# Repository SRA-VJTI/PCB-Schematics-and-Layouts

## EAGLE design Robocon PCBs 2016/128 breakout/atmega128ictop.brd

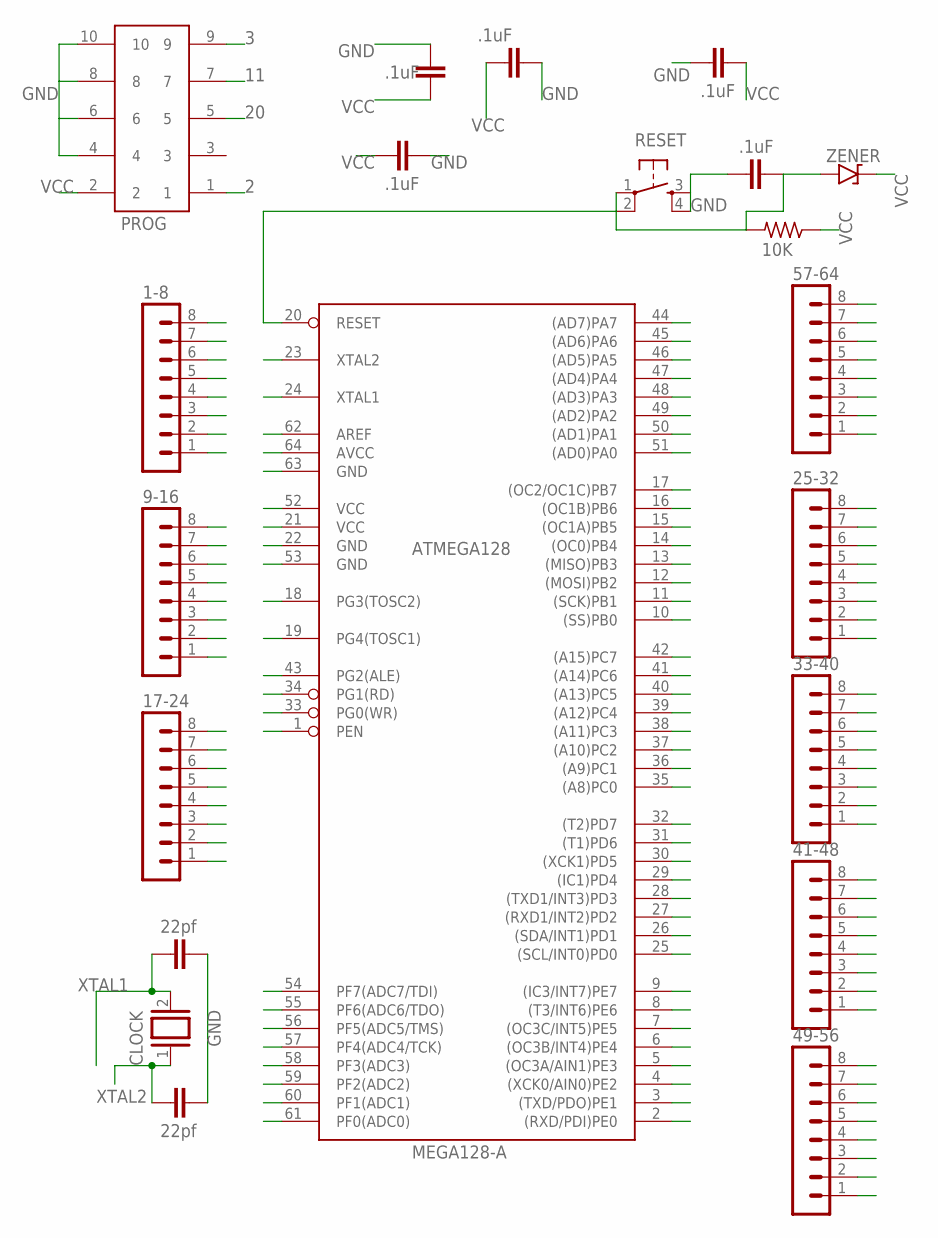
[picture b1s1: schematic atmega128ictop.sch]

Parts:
1-8, 9-16, 17-24, 25-32, 33-40, 41-48, 49-56, 57-64: MA08-1
ATMEGA128: MEGA128-A; TQFP64
C1, C2, C5, C6, C7: .1uF; C5B2.5
C3, C4: 22pf; C5B2.5
CLOCK: XTAL/S; QS
D1: ZENER; DO35-2
PROG: 61201021621
R1: 10K; 0204/5
RESET: DTS-6

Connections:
1: 1-8.1, ATMEGA128.1 (PEN)
2: 1-8.2, ATMEGA128.2 ((RXD/PDI)PE0), PROG.1
3: 1-8.3, ATMEGA128.3 ((TXD/PDO)PE1), PROG.9
4: 1-8.4, ATMEGA128.4 ((XCK0/AIN0)PE2)
5: 1-8.5, ATMEGA128.5 ((OC3A/AIN1)PE3)
6: 1-8.6, ATMEGA128.6 ((OC3B/INT4)PE4)
7: 1-8.7, ATMEGA128.7 ((OC3C/INT5)PE5)
8: 1-8.8, ATMEGA128.8 ((T3/INT6)PE6)
9: 9-16.1, ATMEGA128.9 ((IC3/INT7)PE7)
10: 9-16.2, ATMEGA128.10 ((SS)PB0)
11: 9-16.3, ATMEGA128.11 ((SCK)PB1), PROG.7
12: 9-16.4, ATMEGA128.12 ((MOSI)PB2)
13: 9-16.5, ATMEGA128.13 ((MISO)PB3)
14: 9-16.6, ATMEGA128.14 ((OC0)PB4)
15: 9-16.7, ATMEGA128.15 ((OC1A)PB5)
16: 9-16.8, ATMEGA128.16 ((OC1B)PB6)
17: 17-24.1, ATMEGA128.17 ((OC2/OC1C)PB7)
18: 17-24.2, ATMEGA128.18 (PG3(TOSC2))
19: 17-24.3, ATMEGA128.19 (PG4(TOSC1))
20: 17-24.4, ATMEGA128.20 (RESET), C5.1, D1.A, PROG.5, R1.2, RESET.1, RESET.2
25: 25-32.1, ATMEGA128.25 ((SCL/INT0)PD0)
26: 25-32.2, ATMEGA128.26 ((SDA/INT1)PD1)
27: 25-32.3, ATMEGA128.27 ((RXD1/INT2)PD2)
28: 25-32.4, ATMEGA128.28 ((TXD1/INT3)PD3)
29: 25-32.5, ATMEGA128.29 ((IC1)PD4)
30: 25-32.6, ATMEGA128.30 ((XCK1)PD5)
31: 25-32.7, ATMEGA128.31 ((T1)PD6)
32: 25-32.8, ATMEGA128.32 ((T2)PD7)
33: 33-40.1, ATMEGA128.33 (PG0(WR))
34: 33-40.2, ATMEGA128.34 (PG1(RD))
35: 33-40.3, ATMEGA128.35 ((A8)PC0)
36: 33-40.4, ATMEGA128.36 ((A9)PC1)
37: 33-40.5, ATMEGA128.37 ((A10)PC2)
38: 33-40.6, ATMEGA128.38 ((A11)PC3)
39: 33-40.7, ATMEGA128.39 ((A12)PC4)
40: 33-40.8, ATMEGA128.40 ((A13)PC5)
41: 41-48.1, ATMEGA128.41 ((A14)PC6)
42: 41-48.2, ATMEGA128.42 ((A15)PC7)
43: 41-48.3, ATMEGA128.43 (PG2(ALE))
44: 41-48.4, ATMEGA128.44 ((AD7)PA7)
45: 41-48.5, ATMEGA128.45 ((AD6)PA6)
46: 41-48.6, ATMEGA128.46 ((AD5)PA5)
47: 41-48.7, ATMEGA128.47 ((AD4)PA4)
48: 41-48.8, ATMEGA128.48 ((AD3)PA3)
49: 49-56.1, ATMEGA128.49 ((AD2)PA2)
50: 49-56.2, ATMEGA128.50 ((AD1)PA1)
51: 49-56.3, ATMEGA128.51 ((AD0)PA0)
54: 49-56.6, ATMEGA128.54 (PF7(ADC7/TDI))
55: 49-56.7, ATMEGA128.55 (PF6(ADC6/TDO))
56: 49-56.8, ATMEGA128.56 (PF5(ADC5/TMS))
57: 57-64.1, ATMEGA128.57 (PF4(ADC4/TCK))
58: 57-64.2, ATMEGA128.58 (PF3(ADC3))
59: 57-64.3, ATMEGA128.59 (PF2(ADC2))
60: 57-64.4, ATMEGA128.60 (PF1(ADC1))
61: 57-64.5, ATMEGA128.61 (PF0(ADC0))
62: 57-64.6
GND: 17-24.6, 49-56.5, 57-64.7, ATMEGA128.22 (GND), ATMEGA128.53 (GND), ATMEGA128.63 (GND), C1.1, C2.2, C3.2, C4.2, C5.2, C6.2, C7.2, PROG.4, PROG.6, PROG.8, PROG.10, RESET.3, RESET.4
VCC: 17-24.5, 49-56.4, 57-64.8, ATMEGA128.21 (VCC), ATMEGA128.52 (VCC), ATMEGA128.62 (AREF), ATMEGA128.64 (AVCC), C1.2, C2.1, C6.1, C7.1, D1.C, PROG.2, R1.1
XTAL1: 17-24.8, ATMEGA128.24 (XTAL1), C3.1, CLOCK.2
XTAL2: 17-24.7, ATMEGA128.23 (XTAL2), C4.1, CLOCK.1

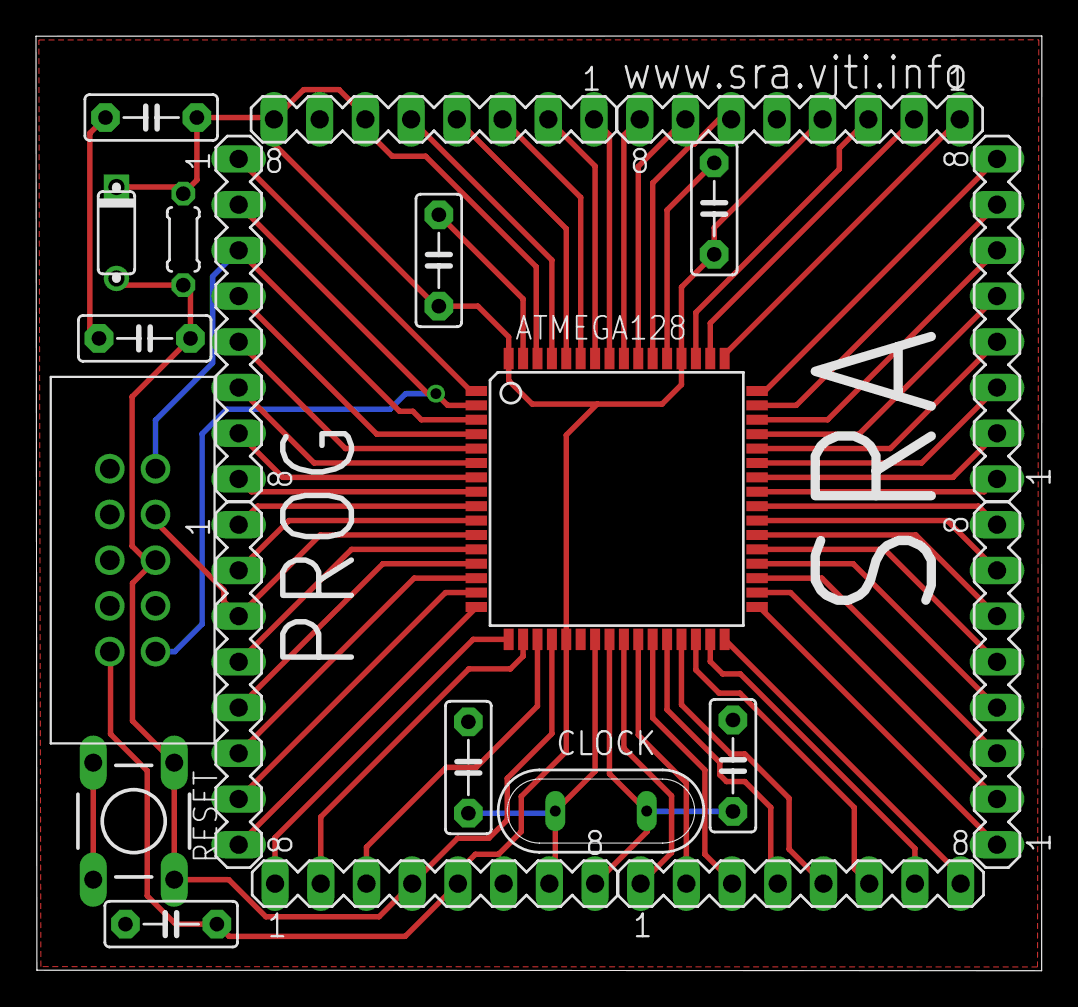
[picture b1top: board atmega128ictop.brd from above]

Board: 2 copper layers, 55.9 x 51.9 mm, 21 parts (0 on the bottom side), 59 nets.

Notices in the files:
parts and their libraries:
Wurth_Elektronik_Electromechanic_Wire_to: Copyright: Würth Elektronik
